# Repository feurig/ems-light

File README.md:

The EMS framework is a forth inspired approach to developing devices built around microcontrollers in the real world. It consists of two major components. 

1. (EMS) A simple mechanism to communicate between the System In Control and the outside world. 

2. (CONSOLE) a cross platform interface (command line or graphical) with the ability to control, log and display the status of the devices subsystems and the ability to update the devices firmware. 

It has been developed around python and the arduino platform with an emphasis on the M0 and the atmega32u4

As a sample application we will controll the lights in the basement......

Automate the lights in the basement based on proximity sensors and investigate smart home, security, and web sockets

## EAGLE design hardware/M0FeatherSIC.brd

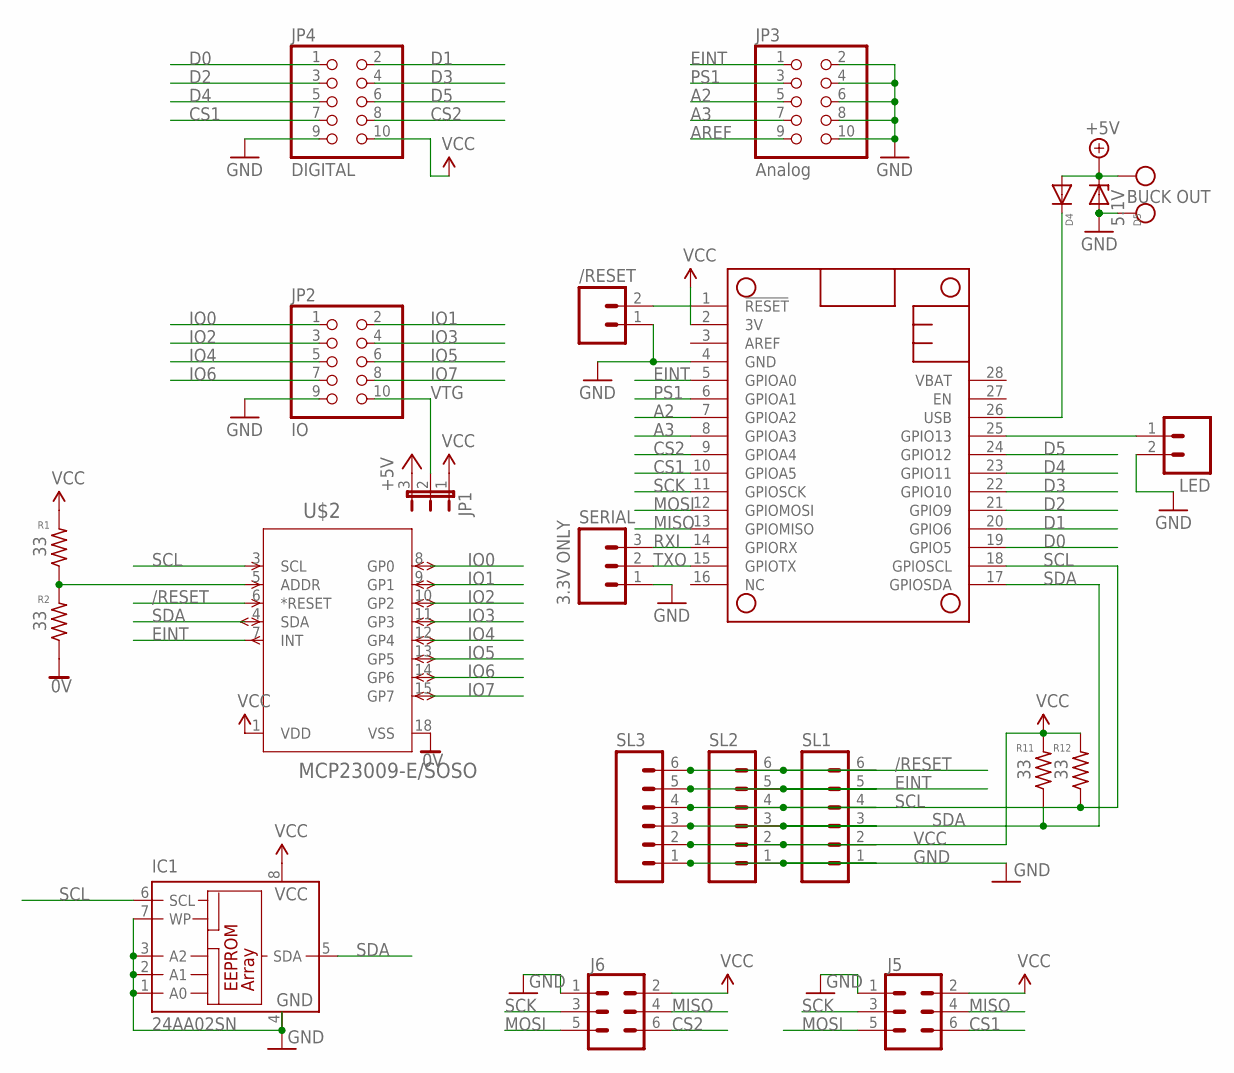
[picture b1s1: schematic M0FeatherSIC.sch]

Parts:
/RESET: M02; 02P
BUCK-OUT: BUCK OUT; W237-102
D4: 1N4148DO35-7; DO35-7
D5: 5.1V; ZDIO-7.5
IC1: 24AA02SN; SO-08
J5, J6: CONN_03X2SHROUD; 2X3-SHROUDED
JP1: JP2E; JP2
JP2: IO; 2X05
JP3: Analog; 2X05
JP4: DIGITAL; 2X05
LED: M02; 02P
MS1: FEATHERWING_NODIM; FEATHERWING_DIM
R1, R2, R11, R12: 33; R0603
SERIAL: 3.3V ONLY; 03P
SL1, SL2, SL3: M06; 06P
U$2: MCP23009-E/SOSO; SOIC18-W_MC

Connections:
0V: R2.1, U$2.18 (VSS)
+5V: BUCK-OUT.1, D4.A, D5.C, JP1.3
/RESET: /RESET.2, MS1.1 (!RESET), SL1.6, SL2.6, SL3.6, U$2.6 (*RESET)
A2: JP3.5, MS1.7 (GPIOA2)
A3: JP3.7, MS1.8 (GPIOA3)
AREF: JP3.9
CS1: J5.6, JP4.7, MS1.10 (GPIOA5)
CS2: J6.6, JP4.8, MS1.9 (GPIOA4)
D0: JP4.1, MS1.19 (GPIO5)
D1: JP4.2, MS1.20 (GPIO6)
D2: JP4.3, MS1.21 (GPIO9)
D3: JP4.4, MS1.22 (GPIO10)
D4: JP4.5, MS1.23 (GPIO11)
D5: JP4.6, MS1.24 (GPIO12)
EINT: JP3.1, MS1.5 (GPIOA0), SL1.5, SL2.5, SL3.5, U$2.7 (INT)
GND: /RESET.1, BUCK-OUT.2, D5.A, IC1.1 (A0), IC1.2 (A1), IC1.3 (A2), IC1.4 (GND), IC1.7 (WP), J5.1, J6.1, JP2.9, JP3.2, JP3.4, JP3.6, JP3.8, JP3.10, JP4.9, LED.2, MS1.4 (GND), SERIAL.1, SL1.1, SL2.1, SL3.1
IO0: JP2.1, U$2.8 (GP0)
IO1: JP2.2, U$2.9 (GP1)
IO2: JP2.3, U$2.10 (GP2)
IO3: JP2.4, U$2.11 (GP3)
IO4: JP2.5, U$2.12 (GP4)
IO5: JP2.6, U$2.13 (GP5)
IO6: JP2.7, U$2.14 (GP6)
IO7: JP2.8, U$2.15 (GP7)
MISO: J5.4, J6.4, MS1.13 (GPIOMISO)
MOSI: J5.5, J6.5, MS1.12 (GPIOMOSI)
unnamed: LED.1, MS1.25 (GPIO13)
unnamed: R1.1, R2.2, U$2.5 (ADDR)
PS1: JP3.3, MS1.6 (GPIOA1)
RXI: MS1.14 (GPIORX), SERIAL.3
SCK: J5.3, J6.3, MS1.11 (GPIOSCK)
SCL: IC1.6 (SCL), MS1.18 (GPIOSCL), R12.1, SL1.4, SL2.4, SL3.4, U$2.3 (SCL)
SDA: IC1.5 (SDA), MS1.17 (GPIOSDA), R11.1, SL1.3, SL2.3, SL3.3, U$2.4 (SDA)
TXO: MS1.15 (GPIOTX), SERIAL.2
USB: D4.C, MS1.26 (USB)
VCC: IC1.8 (VCC), J5.2, J6.2, JP1.1, JP4.10, MS1.2 (3V), R1.2, R11.2, R12.2, SL1.2, SL2.2, SL3.2, U$2.1 (VDD)
VTG: JP1.2, JP2.10

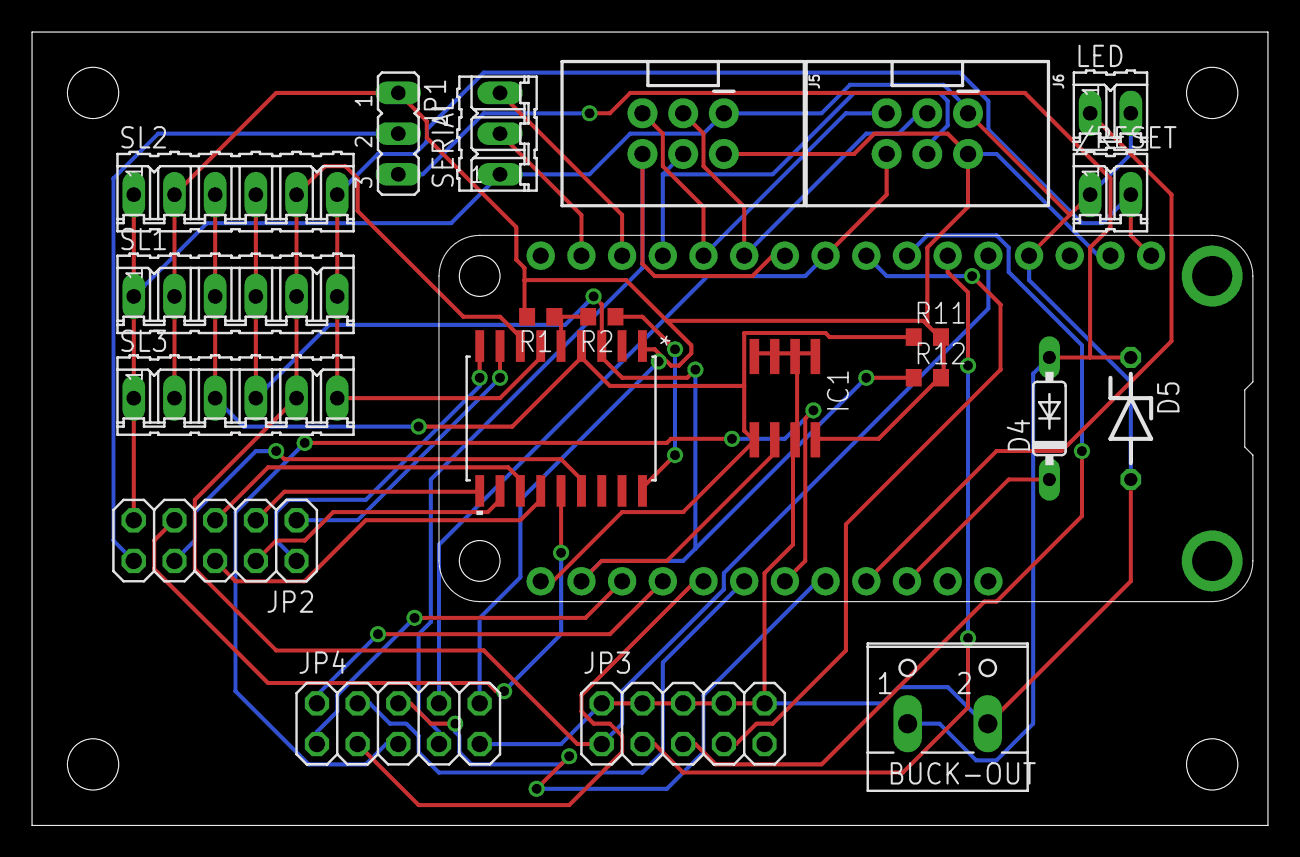
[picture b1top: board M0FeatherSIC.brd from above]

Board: 2 copper layers, 77.1 x 49.5 mm, 22 parts (0 on the bottom side), 36 nets.

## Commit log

2017-10-20 Let's do this
2017-10-21 Move unused modules to ems-templates
2017-10-21 Move machine state constants to Machine.h
2017-10-21 README.md edited online with Bitbucket
2017-10-21 debug it tomorrow
2017-10-27 Generalize EMS as much as possible before implementing gpio and proximity sensors.
2017-10-28 Put Light Curtain Logic back into safety module. Clean up a few things.
2017-10-29 Start Blocking out Processor Specifics.
2017-10-30 generalize jump2bootloader() and reboot() Flesh out reset and jump to boot loader for caterina boot loader (leonardo/micro)
2018-03-04 Cleanup for platformio migration
2018-03-04 ditto
2018-03-04 you are here....
2018-03-04 Platform IO Git Adjustment
2019-01-23 new wxpython syntax
2019-01-24 Update TaskSchedular code
2019-01-24 Need to rework most of the rtc stuff...

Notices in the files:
parts and their libraries:
SparkFun-Connectors: Licensing: CC v3.0 Share-Alike You are welcome to use this library for commercial purposes.
COPYRIGHT: Copyright C 2015 Accelerated Designs. All rights reserved
